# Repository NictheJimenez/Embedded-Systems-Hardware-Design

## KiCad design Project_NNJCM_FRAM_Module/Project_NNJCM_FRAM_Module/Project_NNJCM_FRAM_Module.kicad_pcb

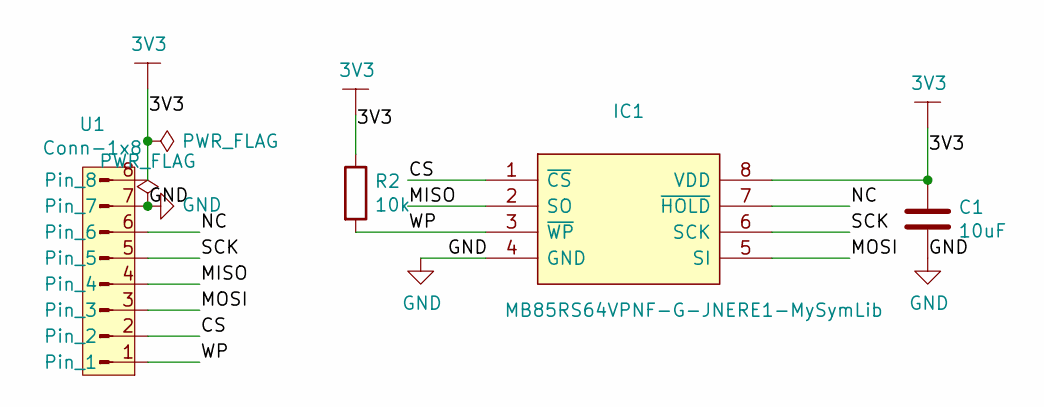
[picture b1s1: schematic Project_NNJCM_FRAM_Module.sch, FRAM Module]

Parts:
C1: 10uF; C_0402_1005Metric
IC1: MB85RS64VPNF-G-JNERE1-MySymLib; SOIC127P600X175-8N; Manufacturer_Part_Number MB85RS64VPNF-G-JNERE1; Mouser Part Number N/A
R2: 10k; R_0402_1005Metric
U1: Conn-1x8; JST_GH_BM08B-GHS-TBT_1x08-1MP_P1.25mm_Vertical

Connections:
+3V3: C1.1, IC1.8 (VDD), R2.1, U1.8
/CS: IC1.1 (~CS), U1.2
/MISO: IC1.2 (SO), U1.4
/MOSI: IC1.5 (SI), U1.3
/NC: IC1.7 (~HOLD), U1.6
/SCK: IC1.6 (SCK), U1.5
/WP: IC1.3 (~WP), R2.2, U1.1
GND: C1.2, IC1.4 (GND), U1.7

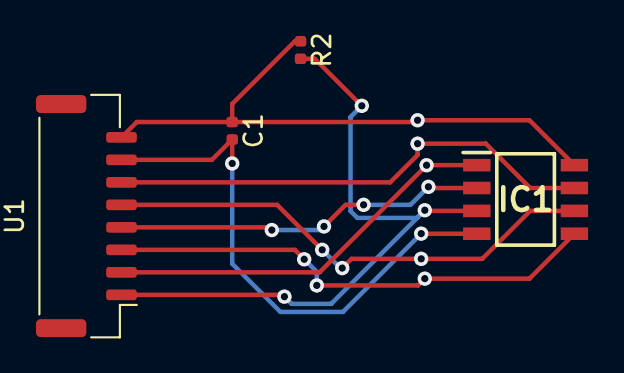
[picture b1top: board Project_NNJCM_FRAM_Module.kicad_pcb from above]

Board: 2 copper layers, 4 parts (0 on the bottom side), 8 nets.

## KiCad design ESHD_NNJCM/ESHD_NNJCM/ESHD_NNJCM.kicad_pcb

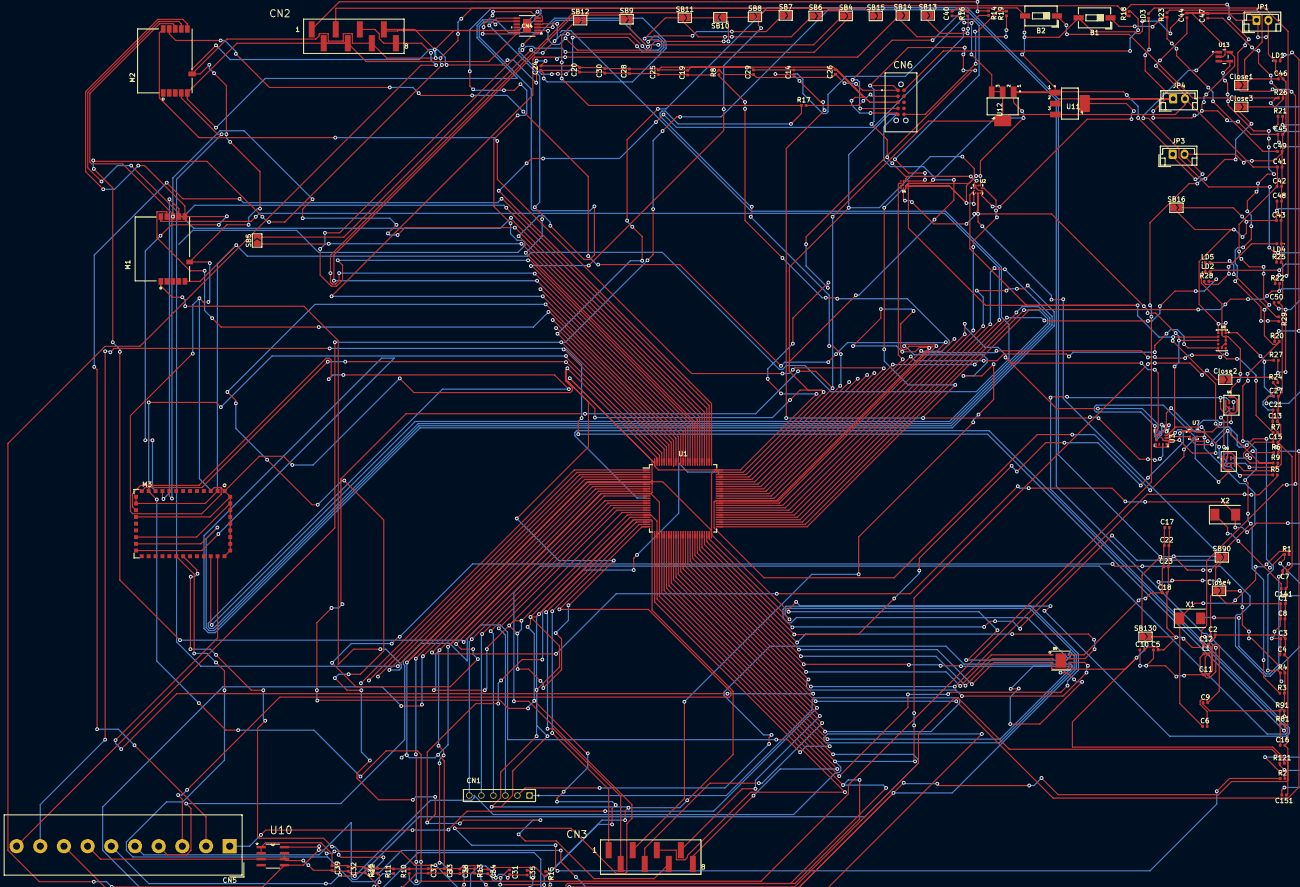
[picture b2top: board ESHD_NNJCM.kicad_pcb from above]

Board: 2 copper layers, 138 parts (0 on the bottom side), 107 nets.

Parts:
B1: SW-PUSH-CMS_BLACK; SW_DIP_SPSTx01_Slide_6.7x4.1mm_W6.73mm_P2.54mm_LowProfile_J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
B2: SW-PUSH-CMS_BLUE; SW_DIP_SPSTx01_Slide_6.7x4.1mm_W6.73mm_P2.54mm_LowProfile_J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
C1, C2, C3, C4, C5, C8, C11, C12, C14, C15, C16, C18, C20, C21, C22, C23, C24, C29, C30, C32, C33, C34, C37, C39, C40, C45, C46, C47, C48: 100nF; C_0402_1005Metric
C6, C7: Not Fitted (8.2pF); C_0402_1005Metric
C9, C10, C17: 1uF; C_0402_1005Metric
C13, C19, C28: 4.7uF; C_0402_1005Metric
C25, C31, C35, C41, C42, C43, C44: 10uF; C_0402_1005Metric
C26: 10uf; C_0402_1005Metric
C27, C36, C38: 2.2uF; C_0402_1005Metric
C49: 10PF; C_0402_1005Metric
C50: 10pF; C_0402_1005Metric
C141, C151: 5.1pF; C_0402_1005Metric
CN1: HEADER_6X1-MTSW-106-07-L-S-105; HEADER_6X1_SAMTEC_MTSW-106-07-L-S-105
CN2: HEADER_8X1-TSM-108-01-S-SV-P-TR-CN2; HEADER_8X1_FEMALE-SAMTEC-TSM-108-01-X-SV
CN3: HEADER_8X1-TSM-108-01-S-SV-P-TR-CN3; HEADER_8X1_FEMALE-SAMTEC-TSM-108-01-X-SV
CN4: HEADER_2X6_PMOD; MSOP-12_MSE-no
CN5: Header_10x1_Femeale-5-534237-8; Altech_AK300_1x10_P5.00mm_45-Degree
CN6: TC2050-IDC-NL; TAG-CONNECT_TC2050-IDC-NL
Close1: SB2; SolderJumper-2_P1.3mm_Open_TrianglePad1.0x1.5mm
Close2: SB1; SolderJumper-2_P1.3mm_Open_TrianglePad1.0x1.5mm
Close3: SB3; SolderJumper-2_P1.3mm_Open_TrianglePad1.0x1.5mm
Close4: SBp; SolderJumper-2_P1.3mm_Open_TrianglePad1.0x1.5mm
JP1: JP; JST_EH_B2B-EH-A_1x02_P2.50mm_Vertical
JP3: JP7; JST_EH_B2B-EH-A_1x02_P2.50mm_Vertical
JP4: IDD; JST_EH_B2B-EH-A_1x02_P2.50mm_Vertical
L1: FTM1608KF-60IT03; L_0402_1005Metric
LD1: LED GREEN; LED_0402_1005Metric
LD2: LED_YELLOW; LED_0402_1005Metric
LD3: LED_BLUE; LED_0402_1005Metric
LD4, LD5: LED_GREEN; LED_0402_1005Metric
M1: SPSGRF; XCVR_SPSGRF-915
M2: ST_SPBTLE_RF; XCVR_SPBTLE-RF
M3: ISM43362-M3G-L44; INVENTEK_ISM43362-M3G-L44-E_C2.5.0.3_SPI
R1, R2: Not Fitted (0R); R_0402_1005Metric
R3, R4, R81, R91: 2k2; R_0402_1005Metric
R5, R6, R15, R121: 0R; R_0402_1005Metric
R7, R8, R24: 10K; R_0402_1005Metric
R9: 10k; R_0402_1005Metric
R10: 47k; R_0402_1005Metric
R11, R12, R13: Not Fitted (10k); R_0402_1005Metric
R14: 1k; R_0402_1005Metric
R16, R17, R18, R19: 22R; R_0402_1005Metric
R20, R28: 330R; R_0402_1005Metric
R21, R23, R26, R29: 1K; R_0402_1005Metric
R22: 680R; R_0402_1005Metric
R25: 200K; R_0402_1005Metric
R27: 100K; R_0402_1005Metric
SB4: close; SolderJumper-2_P1.3mm_Open_TrianglePad1.0x1.5mm
SB5, SB8, SB11, SB12, SB13, SB14, SB15, SB16, SB130: Close; SolderJumper-2_P1.3mm_Open_TrianglePad1.0x1.5mm
SB6, SB7, SB9, SB10, SB90: Open; SolderJumper-2_P1.3mm_Open_TrianglePad1.0x1.5mm
U1: STM32L475VG; LQFP-100_14x14mm_P0.5mm
U2: LPS22HB; LPS22HB_LGA10R50P2X3_200X200X80
U3: LSM6DSLTR; PQFN50P300X250X86-14N
U4: LIS3MDL; LIS3MDL_LGA-12
U5, U6: MP34DT01-M; MIC_MP34DT01-M
U7: HTS221; XDCR_HTS221
U8: VL53L0X; XDCR_VL53L0CXV0DH
U9: MX25R6435F; MX25R6435FZAIH0_SON80P400X400X60-9N
U10: LTI963EST-3.3; LT1963AES8-3.3PBF-SOIC127P600X175-8N
U11: LD1117S33TR; LD1117S33TR-SOT223
U12: LD1117S50TR; LD1117S50TR-SOT223
U13: TSV631AILT; SOT95P280X145-5N
X1: Not Fitted (NX3225GD-8.00M); Crystal_SMD_0603-2Pin_6.0x3.5mm
X2: NX3215SA-32.768K; Crystal_SMD_0603-2Pin_6.0x3.5mm

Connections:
3V3: C9.1, C13.1, C15.1, C16.1, C17.1, C18.1, C19.1, C20.1, C21.1, C22.1, C23.1, C24.1, C25.1, C26.1, C27.1, C28.1, C29.1, C30.1, C32.1, C33.1, C34.1, C35.1, C36.1, C37.1, C38.1, C39.1, C43.1, C45.1, C48.1, CN2.2, CN2.4, CN4.6, CN4.12, CN6.1, Close4.2, JP4.1, LD3.1, M1.5, M2.5, M3.2, M3.14, M3.15, R3.2, R4.2, R7.2, R8.2, R9.1, R10.2, R11.2, R12.2, R27.1, R81.1, R91.1, SB16.1, SB16.2, U1.6, U1.11, U1.28, U1.50, U1.75, U1.100, U2.1, U2.5, U2.6, U2.10, U3.5, U3.8, U3.12, U4.5, U4.6, U4.9, U4.10, U5.1, U6.1, U7.1, U7.6, U8.1, U8.11, U9.8, U10.1, U10.2, U11.2, U11.4, U13.5
5V: C1.1, C2.1, C3.1, C4.1, C5.1, C8.1, C10.1, C11.1, C31.1, C40.1, C41.1, C42.1, C44.1, CN2.5, CN2.8, Close4.1, JP4.2, L1.1, L1.2, R14.2, R15.2, R20.2, SB90.2, U1.21, U1.22, U1.73, U10.5, U10.8, U11.3, U12.2, U12.3, U12.4
ARD.A0-ADC: CN1.01, U1.34
ARD.A1-ADC: CN1.02, U1.33
ARD.A2-ADC: CN1.03, U1.18
ARD.A3-ADC: CN1.04, U1.17
ARD.A4-ADC: CN1.05, U1.16
ARD.A5-ADC: CN1.06, U1.15
ARD.D0-UART4_RX: CN3.1, U1.24
ARD.D1-UART4_TX: CN3.2, U1.23
ARD.D2-INT0_EXTI14: CN3.3, U1.61
ARD.D3-PWM_INTI_EXTI0: CN3.4, U1.35
ARD.D4: CN3.5, U1.26
ARD.D5-PWM: CN3.6, U1.90
ARD.D6-PWM: CN3.7, U1.36
ARD.D7: CN3.8, U1.29
ARD.D8: CN5.1, U1.37
ARD.D9-PWM: CN5.2, U1.77
ARD.D10-SPI_SSN_PWM: CN5.3, U1.25
ARD.D11-SPI1_MOSI_PWM: CN5.4, U1.32
ARD.D12-SPI1_MISO: CN5.5, U1.31
ARD.D13-SPI1_SCK-LED1: CN5.6, Close2.1, U1.30
ARD.D14-I2CI_SDA: CN5.9, R81.2, U1.96
ARD.D15-I2C1_SCL: CN5.10, R91.2, U1.95
BUTTON_EXTI13: Close3.1, U1.7
DFSDM1_CKOUT: R5.2, U1.40
DFSDM1_DATINT: R6.2, U1.38
GND: B1.2, B2.2, C1.2, C2.2, C3.2, C4.2, C5.2, C6.2, C7.1, C8.2, C9.2, C10.2, C11.2, C12.2, C13.2, C14.2, C15.2, C16.2, C17.2, C18.2, C19.2, C20.2, C21.2, C22.2, C23.2, C24.2, C25.2, C26.2, C27.2, C28.2, C29.2, C30.2, C31.2, C32.2, C33.2, C34.2, C35.2, C36.2, C37.2, C38.2, C39.2, C40.2, C41.2, C42.2, C43.2, C44.2, C45.2, C46.2, C47.2, C48.2, C49.2, C50.2, C141.1, C151.1, CN2.6, CN2.7, CN4.5, CN4.11, CN5.7, CN6.3, CN6.5, JP1.1, JP1.2, JP3.1, JP3.2, LD1.1, LD2.1, LD4.1, LD5.1, M1.6, M2.6, M3.1, M3.3, M3.17, M3.20, M3.35, M3.36, M3.37, M3.38, M3.39, M3.40, M3.41, M3.42, M3.43, M3.44, R13.2, R25.2, SB130.2, U1.10, U1.19, U1.20, U1.27, U1.49, U1.74, U1.99, U2.3, U2.8, U2.9, U3.1, U3.6, U3.7, U4.2, U4.3, U4.12, U5.5_1, U5.5_2, U5.5_3, U5.5_4, U6.2, U6.5_1, U6.5_2, U6.5_3, U6.5_4, U7.5, U8.2, U8.3, U8.4, U8.6, U8.12, U9.4, U10.3, U10.6, U10.7, U11.1, U12.1, U13.2
HTS221_DRDY_EXTI15: U1.62, U7.3
INTERNAL-I2C2_SCL: R4.1, U1.47, U2.2, U3.13, U4.1, U7.2, U8.10
INTERNAL-I2C2_SDA: R3.1, U1.48, U2.4, U3.14, U4.11, U7.4, U8.9
INTERNAL-SPI3_MISO: M1.8, M2.8, M3.10, U1.79
INTERNAL-SPI3_MOSI: M1.9, M2.9, M3.9, U1.80
INTERNAL-SPI3_SCK: M1.7, M2.7, M3.11, U1.78
INTERNAL-UART3_RX: M3.22, U1.56
INTERNAL-UART3_TX: M3.21, U1.55
ISM43362-BOOT0: M3.33, U1.51
ISM43362-DRDY_EXTI1: M3.13, U1.98
ISM43362-RST: M3.34, U1.39
ISM43362-SPI3_CSN: M3.12, R10.1, U1.97
ISM43362-WAKEUP: M3.16, U1.52
LED2: R28.2, U1.53
LED3(WIFI)_&_LED4(BLE): R21.2, R22.2, U1.66
LPS22HB_INT_DRDY_EXTI10: U1.57, U2.7
LSM3MDL_DRDY_EXTI8: U1.65, U4.8
LSM6DSL_INT1_EXTI11: U1.58, U3.4
unnamed: B1.1, C49.1, R23.1
unnamed: B2.1, C50.1, R26.1, R27.2
unnamed: C6.1, R1.2, X1.1
unnamed: C7.2, R2.2, X1.2
unnamed: C14.1, U4.4
unnamed: C46.1, Close1.2, R23.2
unnamed: C47.1, Close3.2, R26.2
unnamed: C141.2, R121.1, X2.1
unnamed: C151.2, U1.9, X2.2
unnamed: CN2.1, R14.1
unnamed: CN4.1, SB6.1, SB11.1
unnamed: CN4.2, SB8.1, SB10.1
unnamed: CN4.3, SB4.1, SB9.2
unnamed: CN4.4, SB5.2, SB7.1
unnamed: CN5.8, R15.1
unnamed: CN6.2, R17.2
unnamed: CN6.4, R16.2
unnamed: CN6.6, R19.2
unnamed: CN6.10, R18.2
unnamed: Close2.2, R24.2
unnamed: LD1.2, R20.1
unnamed: LD2.2, R21.1
unnamed: LD3.2, R22.1
unnamed: LD4.2, R28.1
unnamed: LD5.2, R29.1
unnamed: M3.28, R11.1
unnamed: M3.29, R12.1, R13.1
unnamed: R1.1, U1.12
unnamed: R2.1, U1.13
unnamed: R5.1, U5.3, U6.3, U6.4
unnamed: R6.1, U5.4
unnamed: R9.2, U5.2
unnamed: R24.1, R25.1, U13.1
unnamed: R29.2, U13.3, U13.4
unnamed: R121.2, U1.8
unnamed: SB90.1, SB130.1, U1.94
PMOD-IRQ_EXTI2: CN4.7, U1.83
PMOD-RESET: CN4.8, U1.81
PMOD-SPI2_SCK: SB5.1, U1.82
PMOD-UART2_CTS-SPI2_MISO: SB4.2, SB6.2, U1.84
PMOD-UART2_RTS-SPI2_MOSI: SB7.2, SB8.2, U1.85
PMOD-UART2_RX: SB9.1, U1.87
PMOD-UART2_TX-SPI2_CSN: SB10.2, SB11.2, U1.86
QUADSPI_BK1_IO0: U1.43, U9.5
QUADSPI_BK1_IO1: U1.44, U9.2
QUADSPI_BK1_IO2: U1.45, U9.3
QUADSPI_BK1_IO3: U1.46, U9.7
QUADSPI_CLK: U1.41, U9.6
QUADSPI_NCS: U1.42, U9.1
SPBTLE-RF-IRQ_EXTI6: M2.4, U1.5
SPBTLE-RF-RST: M2.11, U1.67
SPBTLE-RF-SPI3_CSN: M2.10, U1.60
SPSGRF-915-GPIO3_EXTI5: M1.1, U1.4
SPSGRF-915-SDN: M1.11, U1.54
SPSGRF-915-SPI3_CSN: M1.10, U1.91
STM_NRST: C12.1, CN2.3, Close1.1, R18.1, SB15.1, U1.14
SYS_JTCK_SWCLK: R16.1, SB13.1, U1.76
SYS_JTDO-SWO: R19.1, SB14.1, U1.89
SYS_JTMS-SWDIO: R17.1, SB12.1, U1.72
VL53L0X_GPIO1_EXT17: R7.1, U1.64, U8.7
VL53L0X_XSHUT: R8.1, U1.63, U8.5

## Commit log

2024-04-03 Source code extracted
